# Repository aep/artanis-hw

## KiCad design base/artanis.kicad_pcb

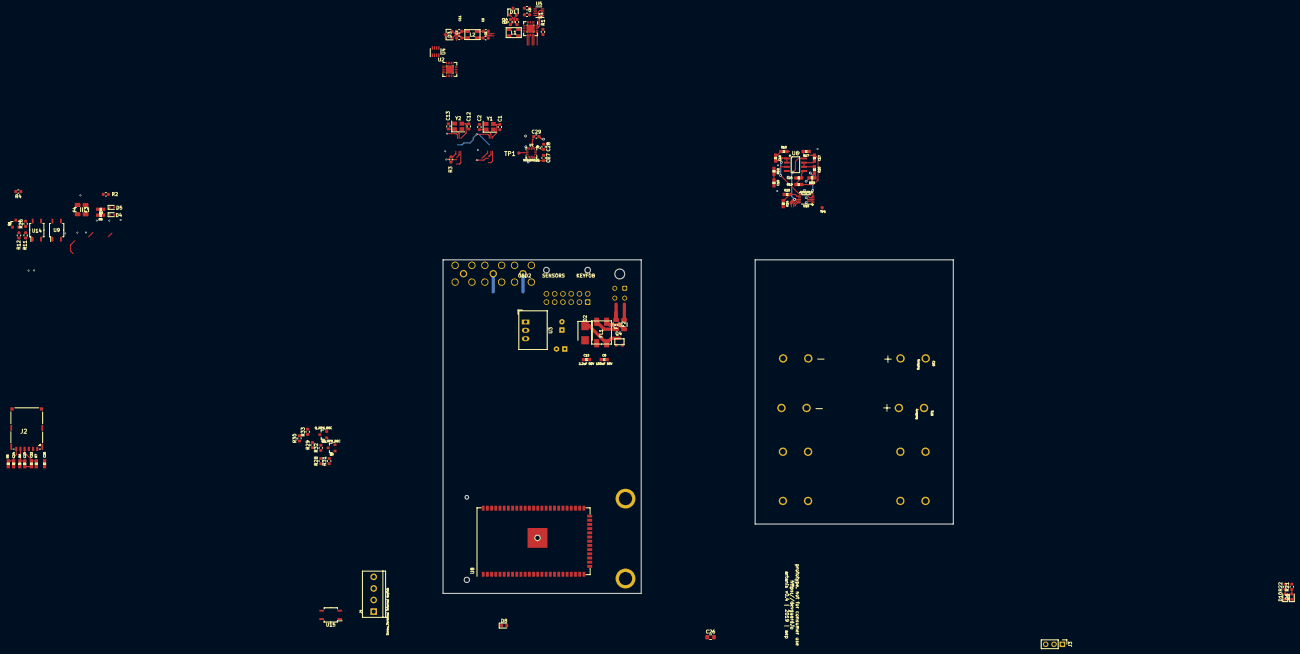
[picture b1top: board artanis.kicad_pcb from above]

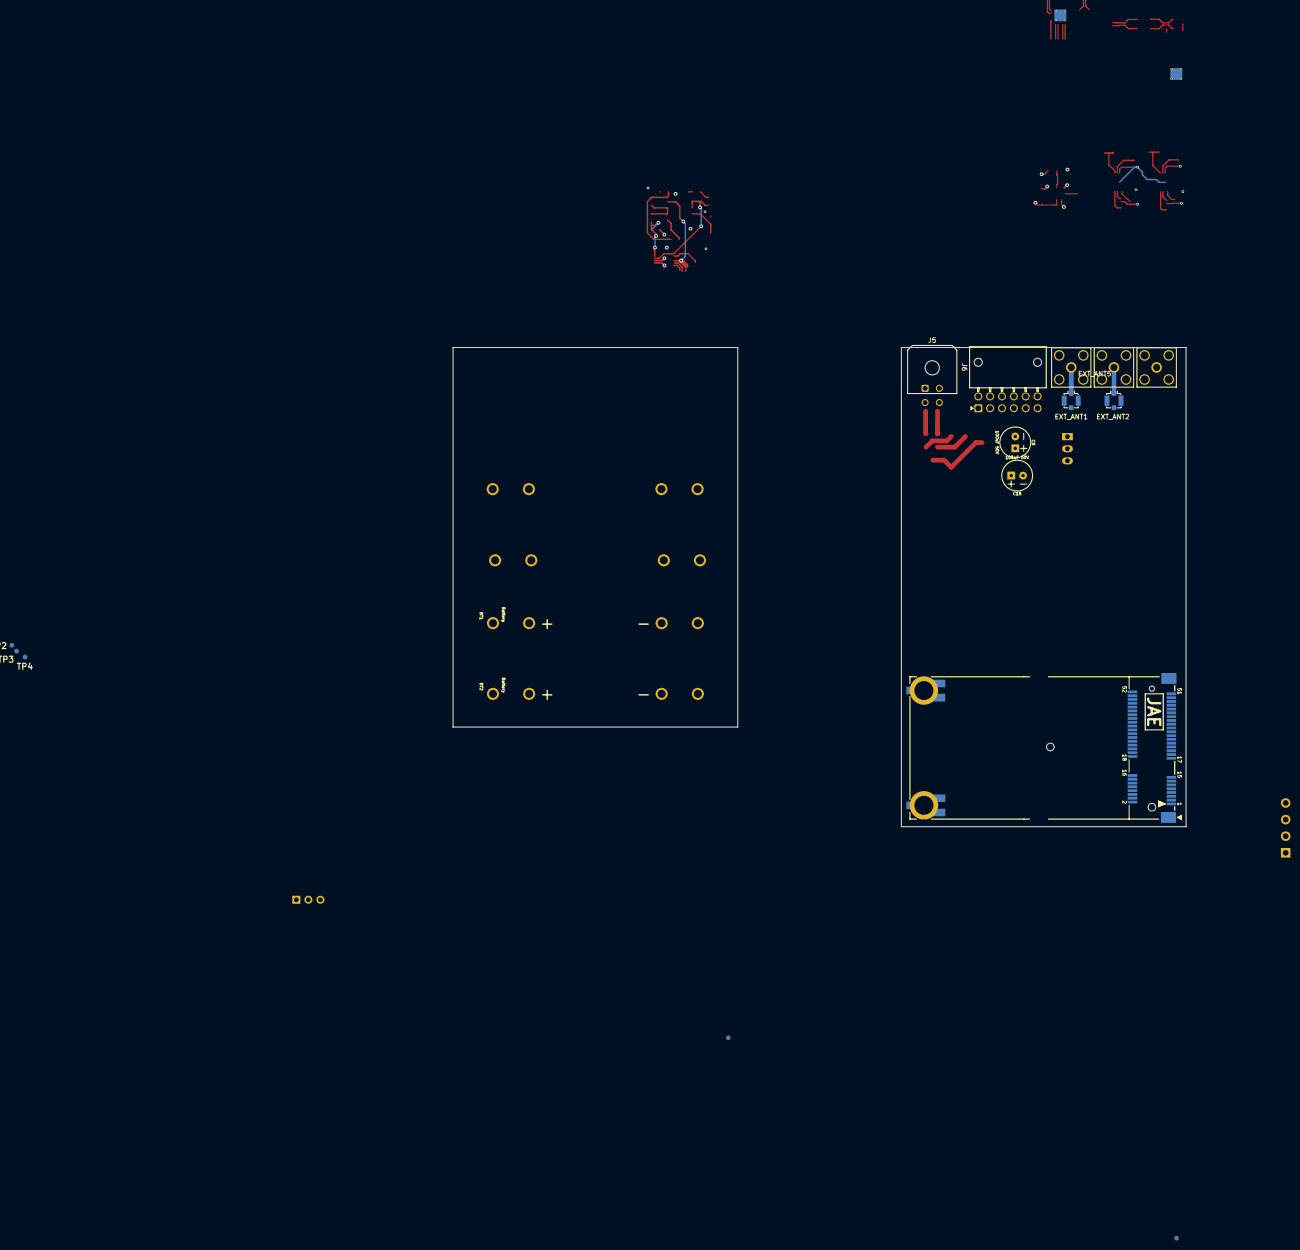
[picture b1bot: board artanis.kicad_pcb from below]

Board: 2 copper layers, 111 parts (17 on the bottom side), 90 nets.

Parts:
BT1, BT1#2, BT2, BT2#2: Battery; BATTERY-AAA
C1, C2, C12, C13: 33pf; C_0603_1608Metric
C3, C4, C5, C6, C7, C11, C14, C15: 56pf; C_0603_1608Metric
C8, C16, C17: 100nF 50V; 0603
C9, C18: 100uF 50V; CPOL-RADIAL-2.5MM-6.5MM
C10: 2.2uF 50V; 0603
C19, C20: 2.2uF; 0603
C22, C23, C24: 33pF; 0603
C25: 100nF; 0603
C26: 10uF; C_0805_2012Metric_Pad1.15x1.40mm_HandSolder
C27: 4.7uF; C_0603_1608Metric
C28, C29: 0.1uF; C_0603_1608Metric
CON1: MSATA-PCIE_MINI-CARD-MM60-52B1-G1-R850(Digi-Key_P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; MM60-52B1-G1-R850
D1, D3: SZNUP2105L; SOT-23
D2: SMBJ16CA-13-F; D_SMB
D4: TVS 3.3V; D_SOD-523
D5: TVS 14V; D_SOD-523
D6, D10: LED; LED_0603_1608Metric
D8: D; D_0603_1608Metric
EXT_ANT1, EXT_ANT2, EXT_ANT5: SMA_F_R_A_PCB; SMA_Amphenol_132203-12_Horizontal
EXT_ANT3, EXT_ANT4: SMA_F_R_A_PCB; U.FL_Molex_MCRF_73412-0110_Vertical
F1, F2, F3, F4: Fuse; Fuse_1206_3216Metric
FID1, FID2: Fiducial; FIDUCIAL-1X2
FL1: ACM70V-701-2PL-TL00; ACM70V
J2: simcard; nanosim-Wurth-693043020611
J3: Conn_01x03; PinHeader_1x03_P2.54mm_Vertical
J4: Screw_Terminal internal keyfob; SCREWTERMINAL-3.5MM-4
J5: Conn_02x02_Top_Bottom; Molex_Micro-Fit_3.0_43045-0400_2x02_P3.00mm_Horizontal
J6: Conn_02x02_Top_Bottom; Molex_Nano-Fit_105314-xx12_2x06_P2.50mm_Horizontal
L1, L2: PE-1210ACC110STS 11UH; PE-1210ACC
Q1, Q3, Q5: Q_NPN_BEC; SOT23-3
Q4: Q_PMOS_GSD; TSMT3
R1, R3: 1K-10K; R_0603_1608Metric
R2, R4: 120 DO NOT POPULATE; R_0603_1608Metric
R5, R6, R7: 45; 0603
R8, R9, R18, R19, R20, R24: 22K; 0603
R10, R17: 3.6K; 0603
R11, R28, R29: 1K; R_0603_1608Metric
R12, R30, R31: 10K; R_0603_1608Metric
R21, R22, R26, R32, R33: R; R_0603_1608Metric
R23, R25: 4.3K; 0603
TP1, TP2, TP3, TP4, TP5: SA0; TP_SMD
U1, U2: MCP2515-QFN; QFN-20-1EP_4x4mm_P0.5mm_EP2.5x2.5mm_ThermalVias
U3: R-78E3.3-1.0; Converter_DCDC_RECOM_R-78E-0.5_THT
U4, U5: TCAN332; SOT-23-8
U6: MCP602; SOIC-8
U7: MMA8452Q; QFN-16
U8: Omega2S; Onion_Omega2S
U9, U14, U15: Omron G3VM-61VY3; SOP-4_3.8x4.1mm_P2.54mm
U10: ADS1015; MSOP10
Y1, Y2: M8AIG-16-12-2T3; Crystal_SMD_Abracon_ABM8G-4Pin_3.2x2.5mm

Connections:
3.3V: C8.2, C10.2, C18.1, C26.2, C27.1, C28.1, CON1.2, CON1.24, CON1.39, CON1.41, CON1.52, D8.2, R1.2, R3.2, R21.2, R22.2, U1.18, U2.18, U3.3, U4.3, U5.3, U6.8, U7.1, U7.14, U8.8, U8.9, U8.32, U9.1, U10.8, U14.1, U15.1
12V: C9.1, Q4.2, R24.1, U3.1
/c1+: C3.1, L1.2, U5.7
/c1-: C4.1, L1.1, U5.6
/c2+: C5.1, L2.2, U4.7
/c2-: C6.1, L2.1, U4.6
/sim_clk: C23.1, J2.C3, R6.1
/sim_data: C24.1, J2.C7, R5.1
/sim_reset: C22.1, J2.C2, R7.1
/sim_vcc: C25.1, CON1.8, J2.C1
/sim_vpp: CON1.16, J2.C6
/xtalc0+: C13.2, U2.7, Y2.1
/xtalc0-: C12.1, U2.6, Y2.3
/xtalc1+: C2.2, U1.7, Y1.1
/xtalc1-: C1.1, U1.6, Y1.3
A1: F3.2, J6.6
A2: F4.1, J6.12
ADC_IRQ: U8.29, U10.2
BATT+: F2.2, J5.1, J5.3
CAN0+: C7.1, D3.1, J5.2, L2.3, R2.1
CAN0-: C11.1, D3.2, J5.4, L2.4, R2.2
CAN0IRQ: U2.11, U8.47
CAN1+: C14.1, D1.1, J6.5, L1.3, R4.1
CAN1-: C15.1, D1.2, J6.11, L1.4, R4.2
CAN1IRQ: U1.11, U8.48
CS0: U2.16, U8.38
CS1: U1.16, U8.45
GND: C1.2, C2.1, C3.2, C4.2, C5.2, C6.2, C7.2, C8.1, C9.2, C10.1, C11.2, C12.2, C13.1, C14.2, C15.2, C18.2, C19.1, C20.1, C22.2, C23.2, C24.2, C25.2, C26.1, C27.2, C28.2, C29.2, CON1.4, CON1.9, CON1.15, CON1.18, CON1.21, CON1.26, CON1.27, CON1.29, CON1.34, CON1.35, CON1.40, CON1.50, CON1.MP1, CON1.MP2, D1.3, D2.2, D3.3, D4.2, D5.2, D10.1, EXT_ANT1.2, EXT_ANT2.2, EXT_ANT3.2, EXT_ANT4.2, EXT_ANT5.2, FL1.4, J2.C5, J2.S, J3.3, J4.4, Q1.2, Q3.2, Q4.1, Q5.2, R12.1, R23.2, R25.2, R30.1, R31.1, U1.8, U1.21, U2.8, U2.21, U3.2, U4.2, U5.2, U6.4, U7.5, U7.10, U7.12, U8.1, U8.22, U8.23, U8.25, U8.63, U8.64, U10.3
IMU_INT1: U7.11, U8.50
IMU_INT2: U7.9, U8.6
KEYFOB_VCC: D8.1, J6.7, J6.8, J6.9, U9.4, U15.4
MISO: U1.15, U2.15, U8.35
MOSI: U1.14, U2.14, U8.36
unnamed: C16.1, R10.1, R18.2
unnamed: C16.2, U6.1, U6.2, U10.4
unnamed: C17.1, R17.1, R19.2
unnamed: C17.2, R20.1, U6.6, U6.7
unnamed: C19.2, R18.1, U6.3
unnamed: C20.2, R19.1, U6.5
unnamed: C29.1, U7.2
unnamed: CON1.10, R5.2
unnamed: CON1.12, R6.2
unnamed: CON1.14, R7.2
unnamed: CON1.42, TP2.1
unnamed: CON1.44, TP3.1
unnamed: CON1.46, TP4.1
unnamed: D2.1, FL1.3, Q4.3
unnamed: D4.1, R8.1, R10.2
unnamed: D5.1, R9.1, R17.2
unnamed: D6.1, U8.19
unnamed: D6.2, R21.1
unnamed: D10.2, R22.1
unnamed: EXT_ANT1.1, EXT_ANT3.1
unnamed: EXT_ANT2.1, EXT_ANT4.1
unnamed: F1.2, FL1.1
unnamed: F2.1, FL1.2
unnamed: F3.1, R8.2
unnamed: F4.2, R9.2
unnamed: J3.1, U8.39
unnamed: J3.2, U8.40
unnamed: Q1.1, R11.1, R12.2
unnamed: Q1.3, R26.1
unnamed: Q3.1, R28.1, R30.2
unnamed: Q3.3, R32.1
unnamed: Q5.1, R29.1, R31.2
unnamed: Q5.3, R33.1
unnamed: R1.1, U1.17
unnamed: R3.1, U2.17
unnamed: R20.2, R23.1, U10.5
unnamed: R24.2, R25.1, U10.6
unnamed: R26.2, U9.2
unnamed: R32.2, U14.2
unnamed: R33.2, U15.2
unnamed: TP1.1, U7.7
unnamed: TP5.1, U10.1
unnamed: U1.19, U5.1
unnamed: U1.20, U5.4
unnamed: U2.19, U4.1
unnamed: U2.20, U4.4
R0O: J4.1, J6.1, U15.3
R1O: J4.2, J4.3, J6.2
R2O: J6.3, U9.3
RELAIS0: R29.2, U8.7
RELAIS2: R11.2, U8.17
RELAIS3: R28.2, U8.18
SCLK: U1.12, U2.12, U8.34
TWI0_SCK: U7.4, U8.30, U10.10
TWI0_SDA: U7.6, U8.31, U10.9
USB2+: CON1.38, U8.61
USB2-: CON1.36, U8.62

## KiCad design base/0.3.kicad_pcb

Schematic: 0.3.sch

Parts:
C1, C2, C3, C4, C11, C12, C13, C14: 56pf; C_0603_1608Metric
C5, C6, C7, C15, C16, C17, C28, C29: 0.1uF; C_0603_1608Metric
C8: 100nF 50V; 0603
C9: 100uF 50V; CPOL-RADIAL-2.5MM-6.5MM
C10: 2.2uF 50V; 0603
C18, C19, C20: 10uF; 0805
C21: 10uF; CP_EIA-7343-31_Kemet-D
C22, C23, C24: 33pF; 0603
C25: 100nF; 0603
C26: 10uF; C_0805_2012Metric_Pad1.15x1.40mm_HandSolder
C27: 4.7uF; C_0603_1608Metric
CON1: MSATA-PCIE_MINI-CARD-MM60-52B1-G1-R850(Digi-Key_P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; MM60-52B1-G1-R850
D1, D3: SZNUP2105L; SOT-23
D2: SMBJ16CA-13-F; D_SMB
D4, D5, D6: LED; LED_0805_2012Metric
D7, D8, D9: PESD5Z70115; D_SOD-523
F1, F2: Fuse; Fuse_1206_3216Metric
FID1: Fiducial; FIDUCIAL-1X2
FL1: ACM70V-701-2PL-TL00; ACM70V
J1: Conn_02x12_Top_Bottom; Molex_Micro-Fit_3.0_43045-2400_2x12_P3.00mm_Horizontal
J2: SIM_Card; microSIM_JAE_SF53S006VCBR2000
K1, K2, K3: G5Q-1A; Relay_SPST_Omron-G5Q-1A
L1, L2: PE-1210ACC110STS 11UH; PE-1210ACC
Q1, Q2, Q3: Q_NPN_BEC; SOT23-3
R1, R3: 120; R_0603_1608Metric
R2, R4, R12, R14, R16: 10K; R_0603_1608Metric
R5, R6, R7: 45; 0603
R8, R9, R10: 330; 0603
R11, R13, R15: 1K; R_0603_1608Metric
R21, R22: 4.7K; R_0603_1608Metric
TP1: SA0; TP_SMD
U1: orange_pi_zero; orangepi-zero
U2, U4: MCP25625-x-SS; QFN-28-1EP_6x6mm_P0.65mm_EP4.25x4.25mm_ThermalVias
U3: OKI-78SR-5_1.5-W36-C; Converter_DCDC_muRata_OKI-78SR_Horizontal
U5: LD1085D2M33R; D2PACK_A
U7: MMA8452Q; QFN-16
Y1, Y2: M8AIG-16-12-2T3; Crystal_SMD_Abracon_ABM8G-4Pin_3.2x2.5mm

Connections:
3.3V: C6.1, C7.1, C16.1, C17.1, C27.1, C28.1, R2.1, R4.2, R21.2, R22.2, U1.101, U1.117, U2.3, U2.11, U4.3, U4.11, U7.1 (VDDIO), U7.14 (VDD)
5V: C5.2, C15.2, C18.1, C26.1, K1.1, K2.1, K3.1, U1.102, U1.104, U2.19, U3.3, U4.19, U5.3
/12v: C8.1, C9.1, C10.1, D2.1 (K), FL1.3, U3.1
/c1_N: C2.1, L1.2, U2.12
/c1_P: C1.1, L1.1, U2.13
/c2_N: C13.1, L2.2, U4.12
/c2_P: C14.1, L2.1, U4.13
/xtalc1+: U4.21, Y2.1
/xtalc1-: U4.20, Y2.3 (2)
/xtalc2+: U2.21, Y1.1
/xtalc2-: U2.20, Y1.3 (2)
BATT+: F2.2, J1.12
BATT-: F1.1, J1.24
CAN0IRQ: U1.122, U4.25
CAN1H: C3.1, D1.2 (K), J1.9, L1.4, R1.1
CAN1IRQ: U1.116, U2.25
CAN1L: C4.1, D1.1 (K), J1.21, L1.3, R1.2
CAN2H: C12.1, D3.2 (K), J1.8, L2.4, R3.1
CAN2L: C11.1, D3.1 (K), J1.20, L2.3, R3.2
CS0: U1.124, U4.1
CS1: U1.118, U2.1
GND: C1.2, C2.2, C3.2, C4.2, C5.1, C6.2, C7.2, C8.2, C9.2, C10.2, C11.2, C12.2, C13.2, C14.2, C15.1, C16.2, C17.2, C18.2, C19.2, C20.2, C21.2, C22.2, C23.2, C24.2, C25.2, C26.2, C27.2, C28.2, C29.2, CON1.4 (GND), CON1.9 (GND), CON1.15 (GND), CON1.18 (GND), CON1.21 (GND), CON1.26 (GND), CON1.27 (GND), CON1.29 (GND), CON1.34 (GND), CON1.35 (GND), CON1.40 (GND), CON1.50 (GND), CON1.MP1 (MOUNTING_PAD), CON1.MP2 (MOUNTING_PAD), D1.3 (A), D2.2 (A), D3.3 (A), D7.2 (A), D8.2 (A), D9.2 (A), FL1.4, J2.5, Q1.2 (E), Q2.2 (E), Q3.2 (E), R12.1, R14.1, R16.1, U1.106, U1.109, U1.114, U1.120, U1.125, U2.18, U2.22, U3.2, U4.18, U4.22, U5.1, U7.5 (GND), U7.10 (GND), U7.12 (GND)
IMU_INT1: U1.112, U7.11 (INT1)
IMU_INT2: U1.111, U7.9 (INT2)
MISO: U1.121, U2.28, U4.28
MOSI: U1.119, U2.27, U4.27
unnamed: C22.1, J2.2, R7.1
unnamed: C23.1, J2.3, R6.1
unnamed: C24.1, J2.7, R5.1
unnamed: C25.1, CON1.8 (RESERVED/UIM_PWR), J2.1
unnamed: C29.1, U7.2 (BYP)
unnamed: CON1.10 (RESERVED/UIM_DATA), R5.2
unnamed: CON1.12 (RESERVED/UIM_CLK), R6.2
unnamed: CON1.14 (RESERVED/UIM_RESET), R7.2
unnamed: CON1.16 (RESERVED/UIM_VPP), J2.6
unnamed: CON1.42 (RESERVED/LED_WWAN#), R8.2
unnamed: CON1.44 (RESERVED/LED_WLAN#), R9.2
unnamed: CON1.46 (RESERVED/LED_WPAN#), R10.2
unnamed: D4.1 (K), R8.1
unnamed: D5.1 (K), R9.1
unnamed: D6.1 (K), R10.1
unnamed: D7.1 (K), K2.5, Q2.3 (C)
unnamed: D8.1 (K), K1.5, Q1.3 (C)
unnamed: D9.1 (K), K3.5, Q3.3 (C)
unnamed: F1.2, FL1.1
unnamed: F2.1, FL1.2
unnamed: Q1.1 (B), R11.1, R12.2
unnamed: Q2.1 (B), R13.1, R14.2
unnamed: Q3.1 (B), R15.1, R16.2
unnamed: R2.2, U2.2
unnamed: R4.1, U4.2
unnamed: TP1.1, U7.7 (SA0)
unnamed: U2.5, U2.10
unnamed: U2.4, U2.16
unnamed: U4.5, U4.10
unnamed: U4.4, U4.16
R1C: J1.14, K1.2
R1O: J1.2, K1.3
R2C: J1.15, K2.2
R2O: J1.3, K2.3
R3C: J1.16, K3.2
R3O: J1.4, K3.3
RELAIS1: R11.2, U1.126
RELAIS2: R13.2, U1.113
RELAIS3: R15.2, U1.115
SCLK: U1.123, U2.26, U4.26
TWI0_SCK: R21.1, U1.105, U7.4 (SCL)
TWI0_SDA: R22.1, U1.103, U7.6 (SDA)
USB2+: CON1.38 (RESERVED/USB_D+), U1.4
USB2-: CON1.36 (RESERVED/USB_D-), U1.3
VCC3V3: C19.1, C20.1, C21.1, CON1.2 (+3.3V/+3.3VAUX), CON1.24 (+3.3V/+3.3VAUX), CON1.39 (+3.3V/+3.3VAUX), CON1.41 (+3.3V/+3.3VAUX), CON1.52 (+3.3V/+3.3VAUX), D4.2 (A), D5.2 (A), D6.2 (A), U5.2, U5.TAB

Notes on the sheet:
Unsafe inputs

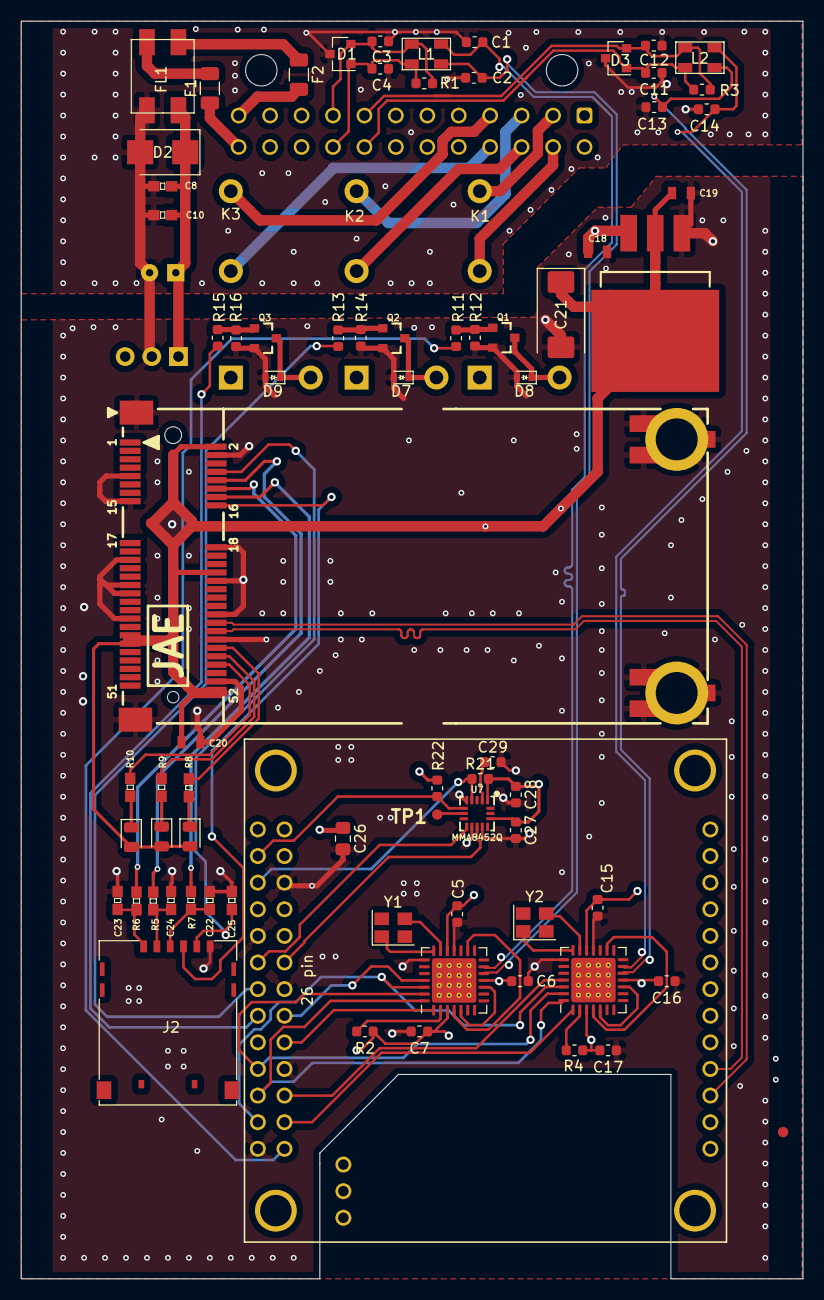
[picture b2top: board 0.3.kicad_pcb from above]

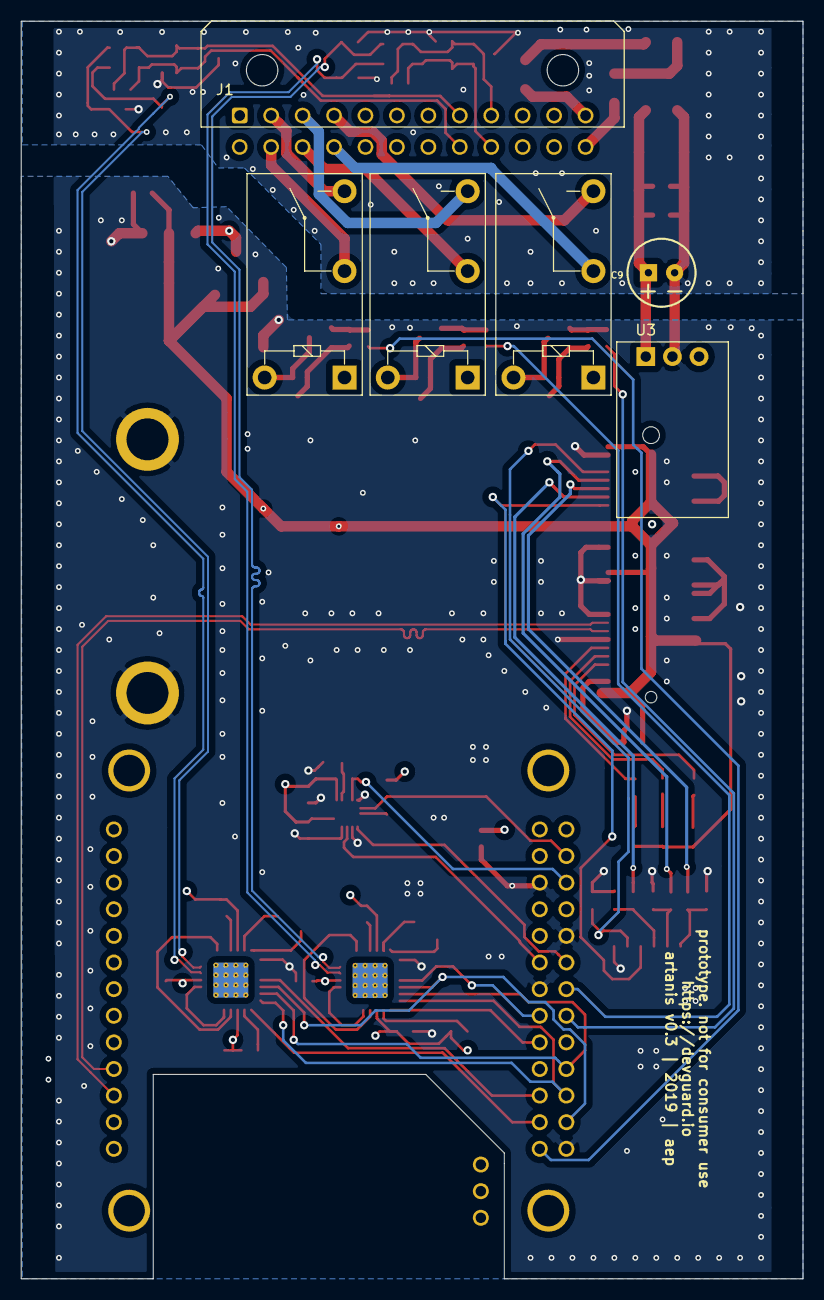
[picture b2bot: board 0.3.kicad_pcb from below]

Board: 4 copper layers, 74.6 x 120.0 mm, 80 parts (6 on the bottom side), 71 nets.
